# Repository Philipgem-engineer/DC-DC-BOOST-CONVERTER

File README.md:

# DC-DC-BOOST-CONVERTER
This repository contains schematic and PCB design of a DC DC BOOST CONVERTER that steps up voltage from 5 V to 12 V. It also contains battery charging circuit.

##  FEATURES
 - INPUT VOLTAGE: 5 V
 - OUTPUT VOLTAGE: 12 V
 - OUTPUT CURRENT: 4 A
 - 97% Efficiency
 - under-voltage lockout, current limiting, and thermal overload protection to prevent damage in the event of an output overload

##  TOOLS USED:
 - Schematic & PCB Design: KiCad
 - Component Library: LCSC
 - PCB Fabrication: JLCPCB

##  SCHEMATIC

##  PCB

##  PCB 3D VIEW

##  MANUFACTURED PCB

## 📁 File Structure

<details>
  <summary>DC-DC Boost Converter</summary>
  <ul>
    <li>
      Media/
      <ul>
        <li>(PDF, images, and videos of prototype)</li>
      </ul>
    </li>
    <li>
      Production Files/
      <ul>
        <li>(Gerber, BOM, positions)</li>
      </ul>
    </li>
    <li>
      KiCad Files/
      <ul>
        <li>(Schematic, PCB, library)</li>
      </ul>
    </li>
  </ul>
</details>

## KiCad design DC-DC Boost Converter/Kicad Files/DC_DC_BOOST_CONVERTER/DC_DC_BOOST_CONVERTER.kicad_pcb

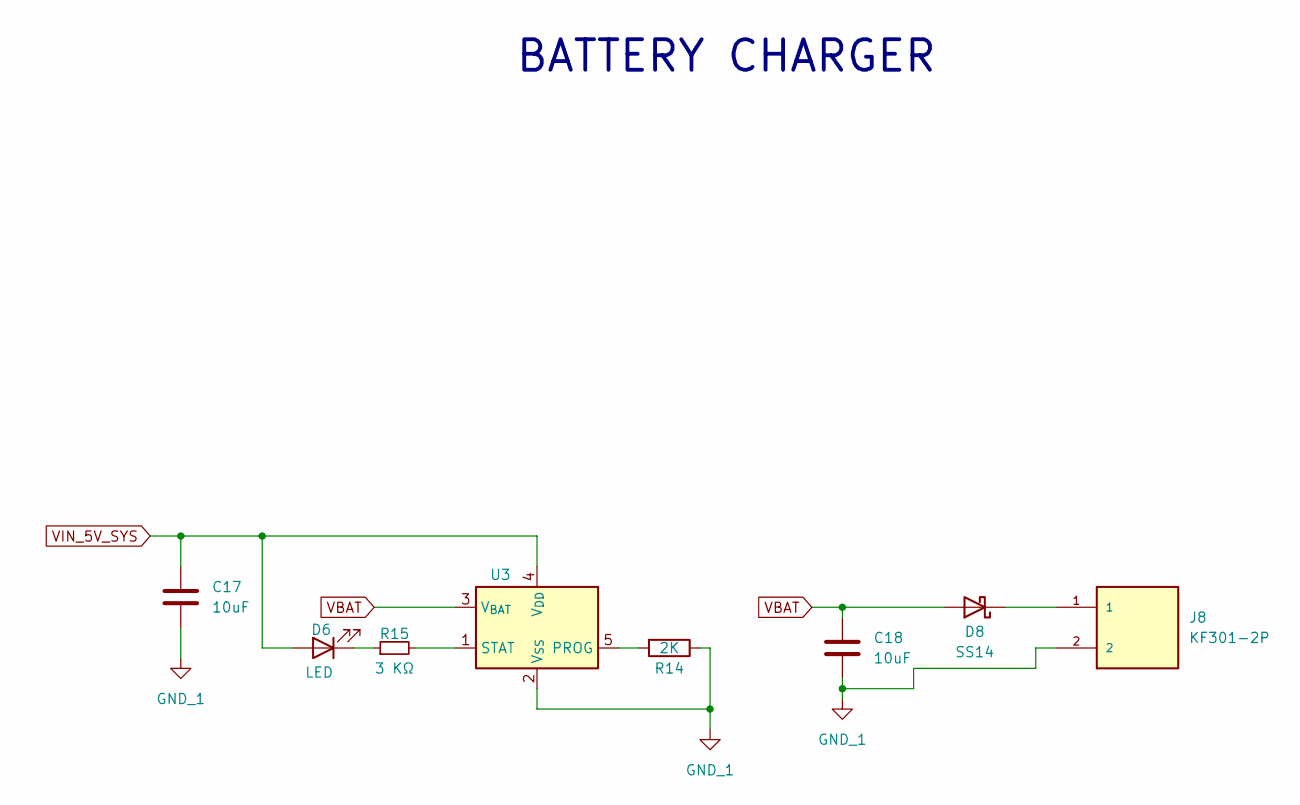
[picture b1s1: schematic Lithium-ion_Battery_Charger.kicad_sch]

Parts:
C17, C18: 10uF; C_0402_1005Metric; MNF PART NUMBER C15525; LCSC C15525
D6: LED; LED_0603_1608Metric; MNF PART NUMBER C2286; LCSC C2286
D8: SS14; D_SMA; MNF PART NUMBER C2480; LCSC C2480
J8: KF301-2P; HANDSON_KF301-2P; PARTREV NA
R14: 2K; R_0402_1005Metric; MNF PART NUMBER C4109; LCSC C4109
R15: 3 KΩ; C_0603_1608Metric; MPN 0603WAF3001T5E; LCSC PN C4211
U3: SOT-23-5; MPN TP4054-42-SOT25R; LCSC PN C32574

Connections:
GND_1: C17.2, C18.2, J8.2, R14.1, U3.2 (V_{SS}); also elsewhere on the board
unnamed: D6.1 (K), R15.1
unnamed: D8.1 (K), J8.1
unnamed: R14.2, U3.5 (PROG)
unnamed: R15.2, U3.1 (STAT)
VBAT: C18.1, D8.2 (A), U3.3 (V_{BAT})
VIN_5V_SYS: C17.1, D6.2 (A), U3.4 (V_{DD}); also elsewhere on the board

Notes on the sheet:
BATTERY CHARGER

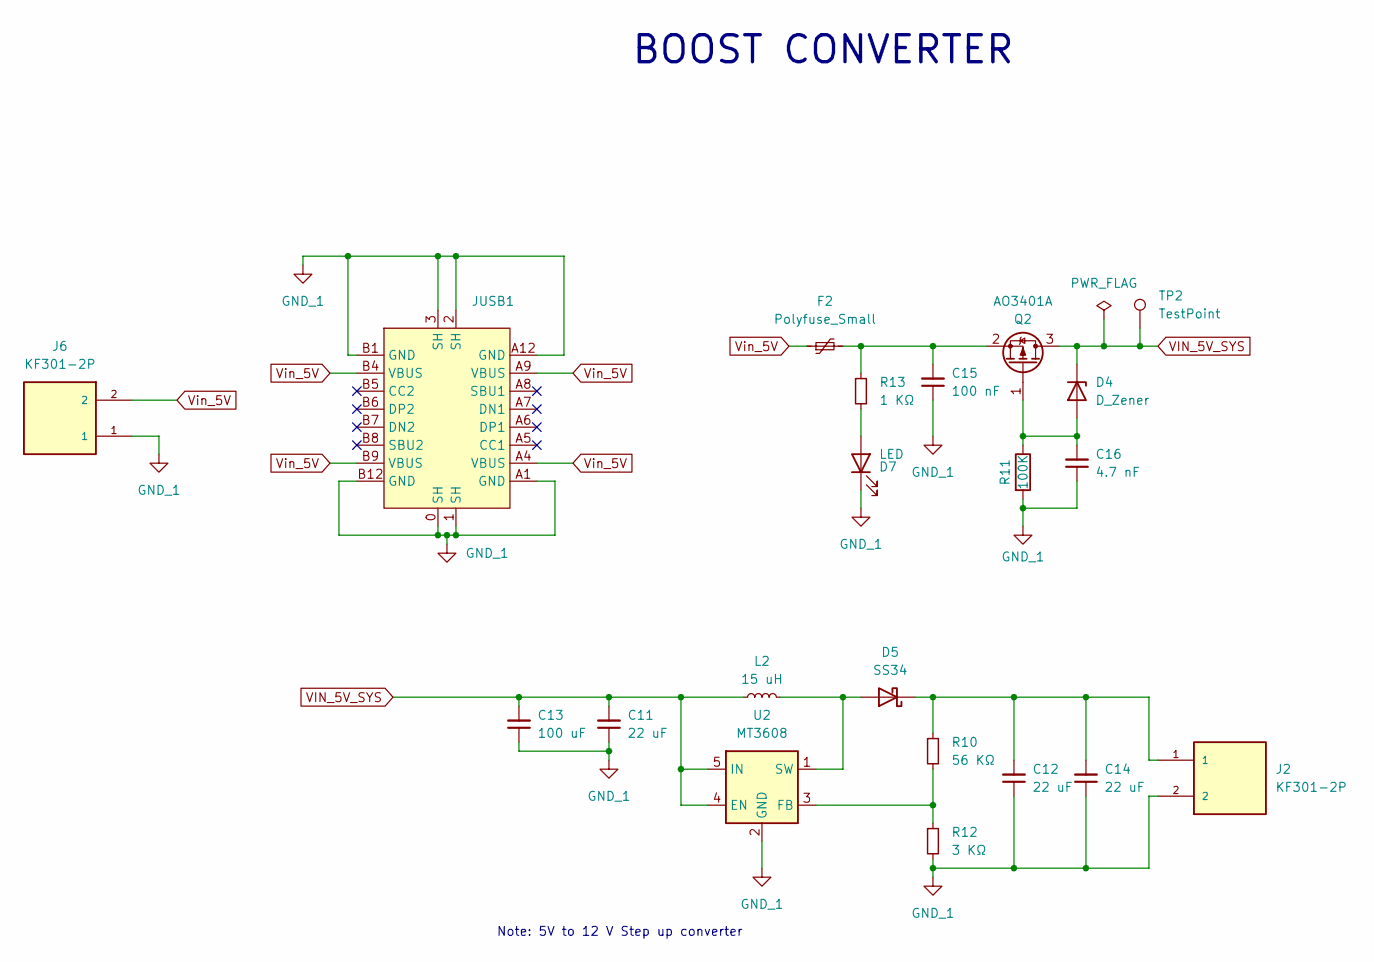
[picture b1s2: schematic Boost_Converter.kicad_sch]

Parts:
C11: 22 uF; C_0603_1608Metric; MPN CL10A226MQ8NRNC; LCSC PN C59461
C12, C14: 22 uF; C_0805_2012Metric; MPN CL21A226MAQNNNE; LCSC PN C45783
C13: 100 uF; C_1206_3216Metric; MPN CL31A107MQHNNNE; LCSC PN C15008
C15: 100 nF; C_0402_1005Metric; MPN CL05B103KB5NNNC; LCSC PN C1525
C16: 4.7 nF; C_0402_1005Metric; MPN 0402B472K500NT; LCSC PN C1538
D4: D_Zener; D_SOD-123; MPN MM1Z5V6; LCSC PN C22395539
D5: SS34; D_SMA; MPN SS34; LCSC PN C8678
D7: LED; LED_0603_1608Metric; MNF PART NUMBER C2286; LCSC C2286
F2: Polyfuse_Small; Fuse_1206_3216Metric; MPN 1206L300SLTHYR; LCSC PN C207041
J2, J6: KF301-2P; HANDSON_KF301-2P; PARTREV NA
JUSB1: USB_TYPE_18; MPN USB-TYPE-C-018; LCSC PN C2927038
L2: 15 uH; L_APV_APH0630; MPN APH0630T150M; LCSC PN C5349699
Q2: AO3401A; SOT-23; MNF PART NUMBER C15127; LCSC C15127
R10: 56 KΩ; C_0603_1608Metric; MPN 0603WAF5602T5E; LCSC PN C23206
R11: 100K; R_0402_1005Metric; MNF PART NUMBER C25741; LCSC C25741
R12: 3 KΩ; C_0603_1608Metric; MPN 0603WAF3001T5E; LCSC PN C4211
R13: 1 KΩ; R_0402_1005Metric; MPN 0402WGF1001TCE; LCSC PN C11702
TP2: TestPoint; TestPoint_Pad_D1.0mm
U2: MT3608; SOT-23-6; MPN MT3608; LCSC PN C84817

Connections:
GND_1: C11.1, C12.1, C13.1, C14.1, C15.1, C16.1, D7.1 (K), J2.2, J6.1, JUSB1.0 (SH), JUSB1.1 (SH), JUSB1.2 (SH), JUSB1.3 (SH), JUSB1.A1 (GND), JUSB1.A12 (GND), JUSB1.B1 (GND), JUSB1.B12 (GND), R11.2, R12.2, U2.2 (GND); also elsewhere on the board
unnamed: C16.2, D4.2 (A), Q2.1 (G), R11.1
unnamed: D5.2 (A), L2.2, U2.1 (SW)
unnamed: C12.2, C14.2, D5.1 (K), J2.1, R10.1
unnamed: D7.2 (A), R13.2
unnamed: C15.2, F2.2, Q2.2 (S), R13.1
unnamed: R10.2, R12.1, U2.3 (FB)
VIN_5V_SYS: C11.2, C13.2, D4.1 (K), L2.1, Q2.3 (D), TP2.1, U2.4 (EN), U2.5 (IN); also elsewhere on the board
Vin_5V: F2.1, J6.2, JUSB1.A4 (VBUS), JUSB1.A9 (VBUS), JUSB1.B4 (VBUS), JUSB1.B9 (VBUS)

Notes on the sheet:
BOOST CONVERTER
Note: 5V to 12 V Step up converter

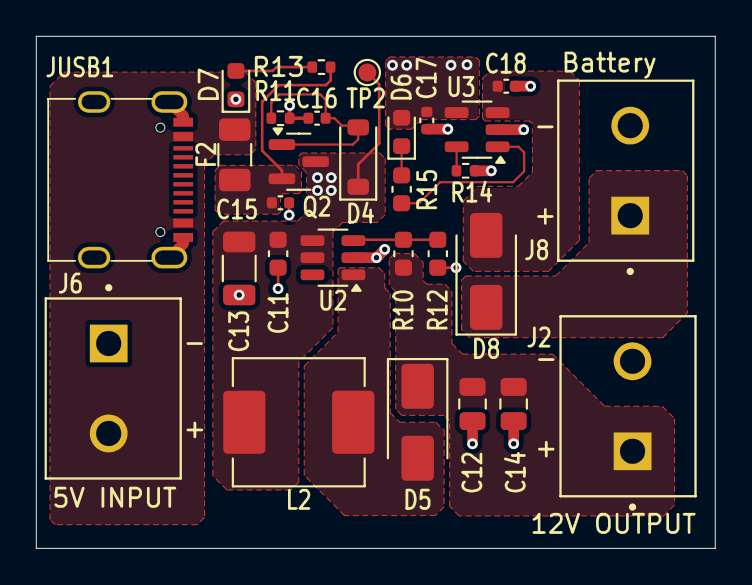
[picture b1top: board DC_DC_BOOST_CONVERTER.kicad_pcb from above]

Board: 2 copper layers, 37.7 x 28.4 mm, 29 parts (0 on the bottom side), 14 nets.
